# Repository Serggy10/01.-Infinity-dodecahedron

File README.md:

# Description
This project consists of an infinity dodecahedron with WS2812B LEDs and an ESP32S3. The device is portable thanks to some batteries with its corresponding BMS. It has connection with Alexa to control colours, modes, brightness and so on.
These are some pictures of the building proccess. Some videos are included in the media folder.

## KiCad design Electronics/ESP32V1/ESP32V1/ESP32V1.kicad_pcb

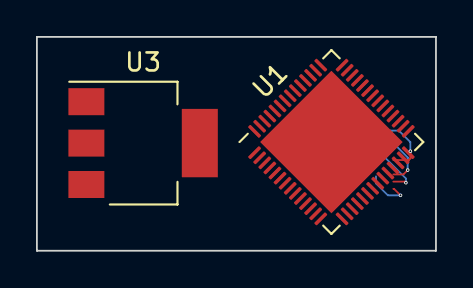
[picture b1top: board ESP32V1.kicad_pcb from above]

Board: 2 copper layers, 22.2 x 11.9 mm, 3 parts (1 on the bottom side), 10 nets.

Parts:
U1: ESP32-S3; QFN-56-1EP_7x7mm_P0.4mm_EP5.6x5.6mm
U2: AT25SF081-SSHD-X; SOIC-8_3.9x4.9mm_P1.27mm
U3: AP1117-33; SOT-223-3_TabPin2

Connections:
/SPICLK: U1.33 (SPICLK/GPIO30), U2.6 (SCK)
/SPICS0: U1.32 (SPICS0/GPIO29), U2.1 (~CS)
/SPID: U1.35 (SPID/GPIO32), U2.5 (SI/IO0)
/SPIHD: U1.30 (SPIHD/GPIO27), U2.7 (~HOLD/IO3)
/SPIQ: U1.34 (SPIQ/GPIO31), U2.2 (SO/IO1)
/SPIWP: U1.31 (SPIWP/GPIO28), U2.3 (~WP/IO2)
/VDD_SPI: U1.29 (VDD_SPI), U2.8 (VCC)
GND: U1.57 (GND), U2.4 (GND)
unnamed: U1.55 (VDDA), U1.56 (VDDA)
VDD3P3: U1.2 (VDD3P3), U1.3 (VDD3P3)

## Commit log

2025-03-06 Initial commit.
2025-07-22 Automatic changes in KiCad files.
2025-08-21 Changed color capability
